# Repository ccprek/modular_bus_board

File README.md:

# modular_bus_board

Kicad files for a Eurorack compatible power bus board. Optional LED indicators and +5V power from supplied +/-12V power.

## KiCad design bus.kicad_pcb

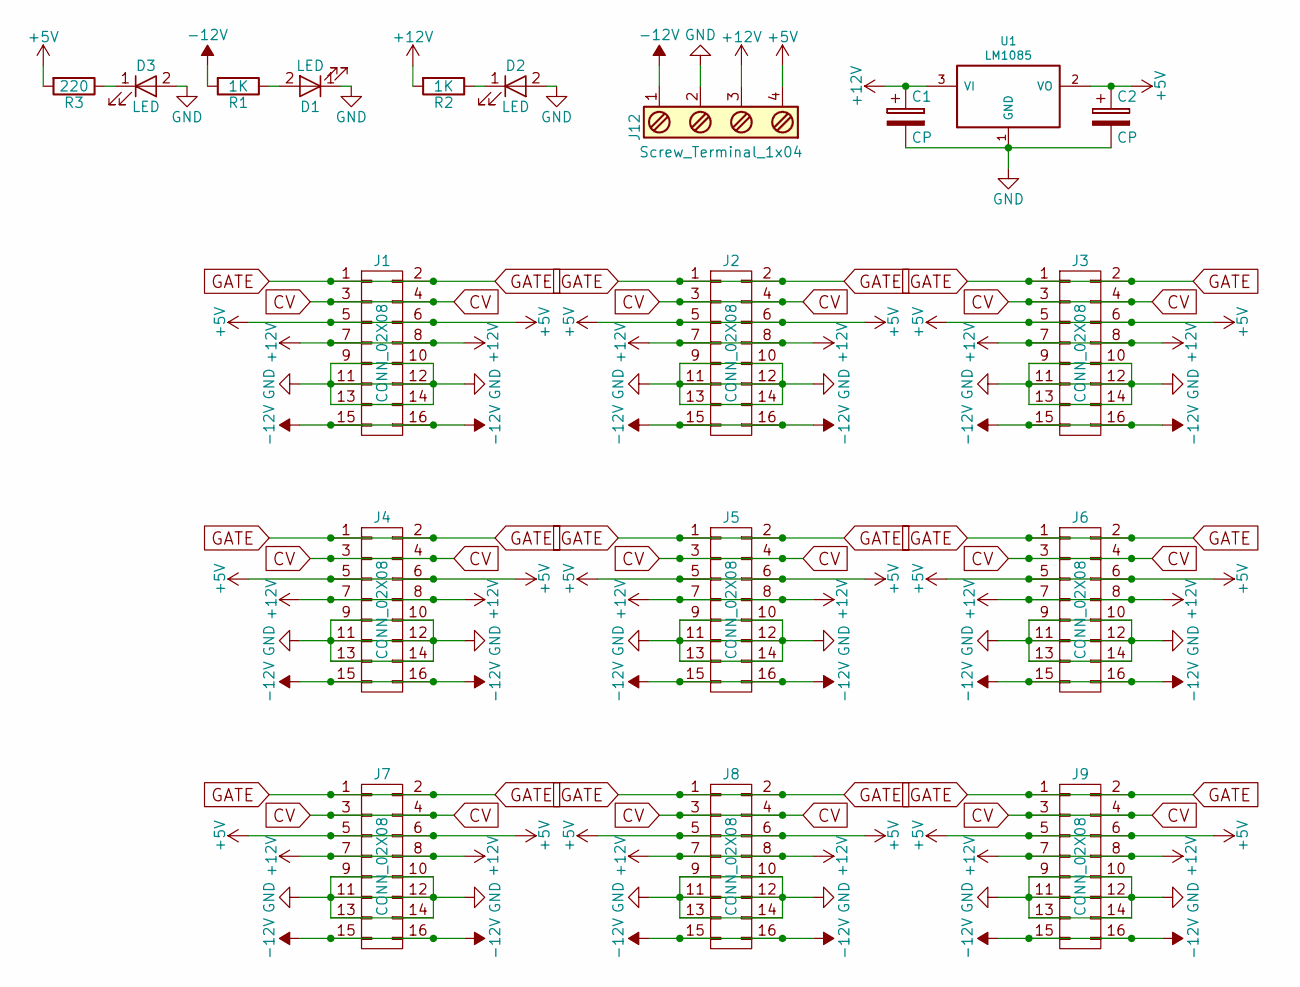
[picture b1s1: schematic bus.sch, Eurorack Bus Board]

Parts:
C1, C2: CP; CP_Radial_D5.0mm_P2.50mm
D1, D2, D3: LED; LED_D5.0mm
J1: CONN_02X08; Socket_Strip_Angled_2x08_Pitch2.54mm
J2, J3, J4, J5, J6, J7, J8: CONN_02X08; IDC_Header_Straight_16pins
J9: CONN_02X08; Pin_Header_Angled_2x08_Pitch2.54mm
J12: Screw_Terminal_1x04; bornier4
R1, R2: 1K; R_Axial_DIN0207_L6.3mm_D2.5mm_P7.62mm_Horizontal
R3: 220; R_Axial_DIN0207_L6.3mm_D2.5mm_P7.62mm_Horizontal
U1: LM1085; TO-220_Vertical

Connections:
+5V: C2.1, J1.5, J1.6, J2.5, J2.6, J3.5, J3.6, J4.5, J4.6, J5.5, J5.6, J6.5, J6.6, J7.5, J7.6, J8.5, J8.6, J9.5, J9.6, J12.4, R3.2, U1.2 (VO); also elsewhere on the board
+12V: C1.1, J1.7, J1.8, J2.7, J2.8, J3.7, J3.8, J4.7, J4.8, J5.7, J5.8, J6.7, J6.8, J7.7, J7.8, J8.7, J8.8, J9.7, J9.8, J12.3, R2.2, U1.3 (VI); also elsewhere on the board
-12V: J1.15, J1.16, J2.15, J2.16, J3.15, J3.16, J4.15, J4.16, J5.15, J5.16, J6.15, J6.16, J7.15, J7.16, J8.15, J8.16, J9.15, J9.16, J12.1, R1.2; also elsewhere on the board
CV: J1.3, J1.4, J2.3, J2.4, J3.3, J3.4, J4.3, J4.4, J5.3, J5.4, J6.3, J6.4, J7.3, J7.4, J8.3, J8.4, J9.3, J9.4; also elsewhere on the board
GATE: J1.1, J1.2, J2.1, J2.2, J3.1, J3.2, J4.1, J4.2, J5.1, J5.2, J6.1, J6.2, J7.1, J7.2, J8.1, J8.2, J9.1, J9.2; also elsewhere on the board
GND: C1.2, C2.2, D1.1 (K), D2.2 (A), D3.2 (A), J1.9, J1.10, J1.11, J1.12, J1.13, J1.14, J2.9, J2.10, J2.11, J2.12, J2.13, J2.14, J3.9, J3.10, J3.11, J3.12, J3.13, J3.14, J4.9, J4.10, J4.11, J4.12, J4.13, J4.14, J5.9, J5.10, J5.11, J5.12, J5.13, J5.14, J6.9, J6.10, J6.11, J6.12, J6.13, J6.14, J7.9, J7.10, J7.11, J7.12, J7.13, J7.14, J8.9, J8.10, J8.11, J8.12, J8.13, J8.14, J9.9, J9.10, J9.11, J9.12, J9.13, J9.14, J12.2, U1.1 (GND); also elsewhere on the board
unnamed: D1.2 (A), R1.1
unnamed: D2.1 (K), R2.1
unnamed: D3.1 (K), R3.1

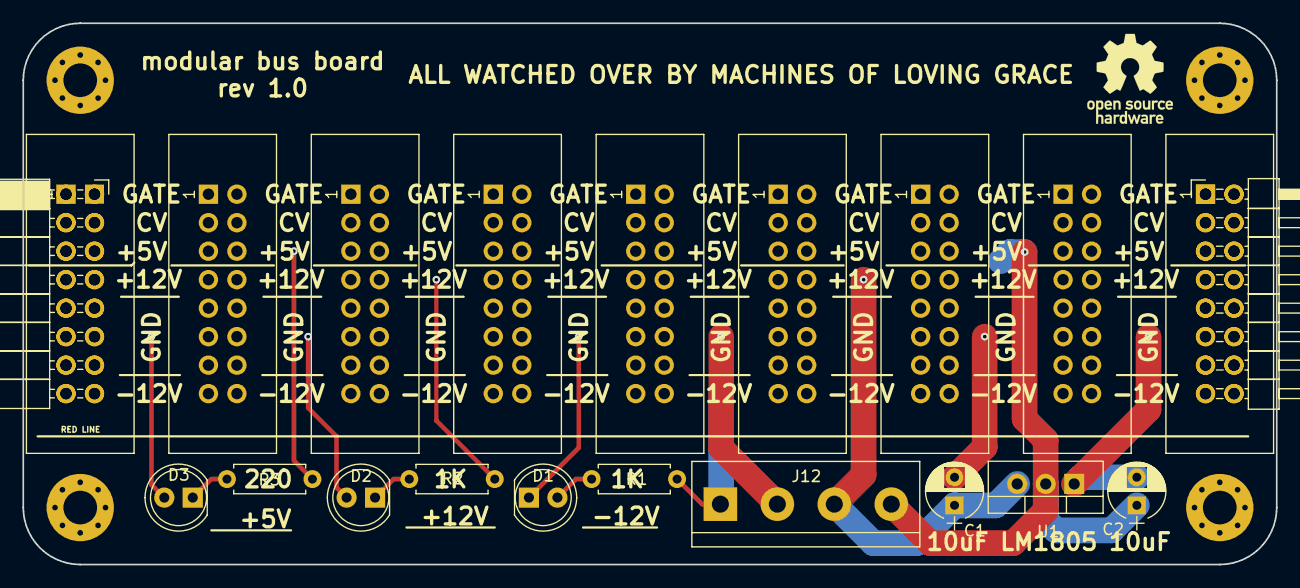
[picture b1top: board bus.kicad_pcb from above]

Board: 2 copper layers, 111.8 x 48.3 mm, 21 parts (0 on the bottom side), 9 nets.

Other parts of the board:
J2#2, J8#2: CONN_02X08; IDC_Header_Straight_16pins

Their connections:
+5V: J2#2.5, J2#2.6, J8#2.5, J8#2.6; also elsewhere on the board
+12V: J2#2.7, J2#2.8, J8#2.7, J8#2.8; also elsewhere on the board
-12V: J2#2.15, J2#2.16, J8#2.15, J8#2.16; also elsewhere on the board
CV: J2#2.3, J2#2.4, J8#2.3, J8#2.4; also elsewhere on the board
GATE: J2#2.1, J2#2.2, J8#2.1, J8#2.2; also elsewhere on the board
GND: J2#2.9, J2#2.10, J2#2.11, J2#2.12, J2#2.13, J2#2.14, J8#2.9, J8#2.10, J8#2.11, J8#2.12, J8#2.13, J8#2.14; also elsewhere on the board

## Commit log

2017-06-28 Added all files
2017-06-28 added render to README.md
2017-06-28 Create LICENSE
2017-06-30 Moved LM1085 and silkscreen label clean-up
